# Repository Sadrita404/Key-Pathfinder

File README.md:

| Title | Key Pathfinder |
| :-- | :---|
|Author |Sadrita Neogi|

### About
A small basic strategy machine using only 4 buttons and 4 leds. It uses a Seeed Studios Xiao RP2040 for logic it is also use to control the keyboard shortcuts.

### Why I chose this project?
Behind choosing this project, when I have started stasis I was not sure about what I can. Then. I see the starter project where I find this pathfinder that to be built, so I make it with some extra features like in the starter project, it has only three keys, so I added one extra keys just to use the more functionality of the device, so I have build this project.

### How to use this project
This project can be used in multiple waste based upon the user need best for me. I will use it for the shortcut that I have implemented and also it also works as a stress reliever. When I am bored, I can place the key and the LED will blink, according to the input that I am giving.

<div align="center">

| | PCB Designing | |
| :---: | :---: | :---: |
|  |  |  |
|  |  |  |
|  |  |  |

<!-- TWO-COLUMN IMAGE FRAME GRID -->
<div align="center">
  <table border="0" cellpadding="10" cellspacing="0" style="border-collapse: collapse;">
    <tr>
      <!-- FRONT SIDE CARD -->
      <td align="center" valign="top" width="50%" style="background: #ffffff; border: 1px solid #d0d7de; border-radius: 12px; padding: 16px; box-shadow: 0 4px 12px rgba(0,0,0,0.05);">
        
        <div style="margin-top: 12px; font-family: -apple-system, BlinkMacSystemFont, 'Segoe UI', Helvetica, Arial, sans-serif; font-size: 13px; color: #57606a; font-weight: 600; text-transform: uppercase; letter-spacing: 0.5px;">
          ▲ Front Side View
        </div>
      </td>
      <!-- SPACER FOR GITHUB MOBILE DEGRADATION -->
      <td width="2%">&nbsp;</td>
      <!-- BACK SIDE CARD -->
      <td align="center" valign="top" width="50%" style="background: #ffffff; border: 1px solid #d0d7de; border-radius: 12px; padding: 16px; box-shadow: 0 4px 12px rgba(0,0,0,0.05);">
        
        <div style="margin-top: 12px; font-family: -apple-system, BlinkMacSystemFont, 'Segoe UI', Helvetica, Arial, sans-serif; font-size: 13px; color: #57606a; font-weight: 600; text-transform: uppercase; letter-spacing: 0.5px;">
          ▲ Back Side View
        </div>
      </td>
    </tr>
  </table>
</div>
</div>

<div align="center">
  <h2> Bill of Materials </h2>
</div>

| Component Name | Purpose | Qty | Unit Price | Total Price in USD | Link |
| :--- | :--- | :---: | :---: | :---: | :---: |
| **Resistors(220 Ohm 0.25W )** | To control the current flow | 4 | $0.0096 | $0.04 | [Link](https://robu.in/product/220-ohm-resistor-0-25w-metal-film-pack-of-100/?gad_source=1&gad_campaignid=17427802703&gbraid=0AAAAADvLFWekTwWN9jC03A8IQT8r3AlY5&gclid=CjwKCAjw6f3RBhApEiwAMaCqWcaO2dly3_fFTVA-yL3R27B3th02OcCqODYx5UqYKDzOy5vnEFLU-hoCv24QAvD_BwE) |
| **3mm Green DIP LED** | For the light | 4 | $0.016 | $0.06 | [Link](https://robu.in/product/5mm-green-surface-mount-led-pack-of-50/?gad_source=1&gad_campaignid=17427802703&gbraid=0AAAAADvLFWekTwWN9jC03A8IQT8r3AlY5&gclid=CjwKCAjw6f3RBhApEiwAMaCqWRUCdY8CmAQTw0-cabIrtaeX7ebfmDpTQ9LgE_gcqU91_RtSVQTk3hoCW7cQAvD_BwE)|
| **Blank Keycaps (10)** | To put it in the switches | 1 | $1.59 | $1.59 | [Link](https://stackskb.com/store/numpad-keycaps/) |
| **Seeed Studio XIAO RP2040** | To control the board | 1 | $6.55 | $6.55 | [Link](https://robu.in/product/seeed-studio-xiao-rp2040-v1-0/) |
| **PCB Board** | The main board | 1 | $2.00 | $2.00 | [Link](https://jlcpcb.com/) |
| **Linear Switch (moq 10)** | To press the switch | 1 | $3.18 | $3.18 | [Link](https://stackskb.com/store/hmx-switch-tester/) |

<div align="center">
  <table border="0" cellpadding="0" cellspacing="0" style="border-collapse: collapse; max-width: 600px;">
    <tr>
      <td style="background: #ffffff; border: 1px solid #d0d7de; border-radius: 12px; padding: 20px; box-shadow: 0 4px 12px rgba(0,0,0,0.05); font-family: -apple-system, BlinkMacSystemFont, 'Segoe UI', Helvetica, Arial, sans-serif;">
        <div style="font-size: 16px; font-weight: 600; color: #24292f; margin-bottom: 12px; border-bottom: 1px solid #d0d7de; padding-bottom: 8px;">
           Final Summary Title
        </div>
        <table width="100%" border="0" style="border-collapse: collapse; font-size: 14px; color: #57606a;">
          <tr>
            <td style="padding: 4px 0;">Component Subtotal:</td>
            <td align="right" style="font-weight: 500; color: #24292f;">$13.42</td>
          </tr>
          <tr>
            <td style="padding: 4px 0;">Shipping Cost(incl. PCB):</td>
            <td align="right" style="font-weight: 500; color: #24292f;">$11</td>
          </tr>
          <tr>
            <td style="padding: 4px 0; padding-bottom: 8px;">Tax:</td>
            <td align="right" style="font-weight: 500; color: #24292f;">$0.5</td>
          </tr>
          <tr style="border-top: 1px dashed #d0d7de;">
            <td style="padding: 12px 0 0 0; font-weight: 600; color: #24292f; font-size: 15px;">Net Total Cost:</td>
            <td align="right" style="padding: 12px 0 0 0; font-weight: bold; color: #2da44e; font-size: 18px;">$24.92</td>
          </tr>
          <tr>
            <td style="padding: 2px 0 0 0; font-size: 11px; color: #8c959f;">Projected Budget Allocation:</td>
            <td align="right" style="padding: 2px 0 0 0; font-weight: 500; font-size: 12px; color: #8c959f;">$25</td>
          </tr>
        </table>
      </td>
    </tr>
  </table>
</div>

---

**Project Under Hack Club**

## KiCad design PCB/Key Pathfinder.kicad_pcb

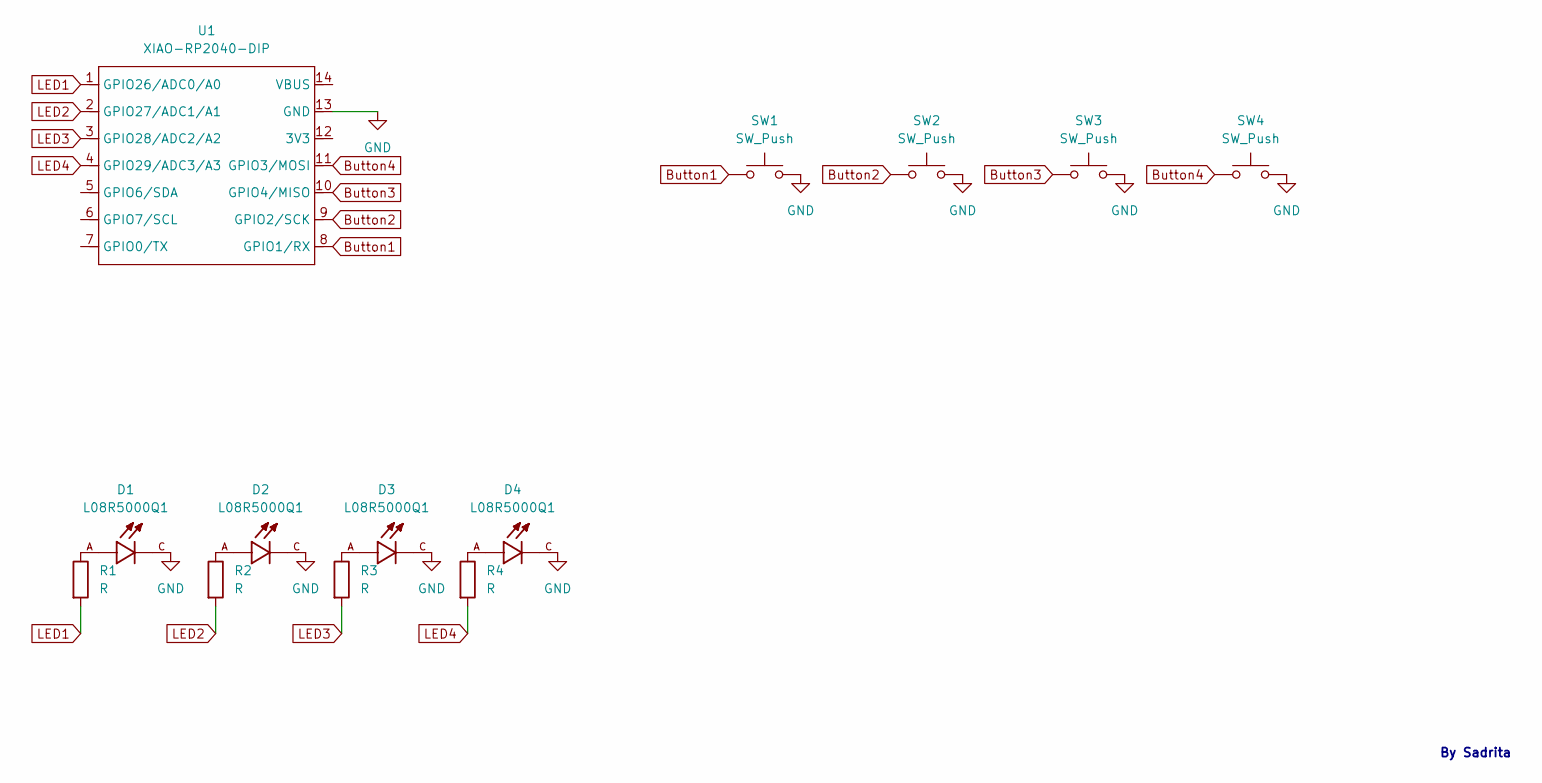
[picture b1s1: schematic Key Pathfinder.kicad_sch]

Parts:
D1, D2, D3, D4: L08R5000Q1; LED; PARTREV NA
R1, R2, R3, R4: R; R_Axial_DIN0204_L3.6mm_D1.6mm_P5.08mm_Vertical
SW1, SW2, SW3, SW4: SW_Push; SW_Cherry_MX_1.00u_PCB3D
U1: XIAO-RP2040-DIP

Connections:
Button1: SW1.1, U1.8 (GPIO1/RX)
Button2: SW2.1, U1.9 (GPIO2/SCK)
Button3: SW3.1, U1.10 (GPIO4/MISO)
Button4: SW4.1, U1.11 (GPIO3/MOSI)
GND: D1.C, D2.C, D3.C, D4.C, SW1.2, SW2.2, SW3.2, SW4.2, U1.13 (GND)
LED1: R1.2, U1.1 (GPIO26/ADC0/A0)
LED2: R2.2, U1.2 (GPIO27/ADC1/A1)
LED3: R3.2, U1.3 (GPIO28/ADC2/A2)
LED4: R4.2, U1.4 (GPIO29/ADC3/A3)
unnamed: D1.A, R1.1
unnamed: D2.A, R2.1
unnamed: D3.A, R3.1
unnamed: D4.A, R4.1

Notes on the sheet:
By Sadrita

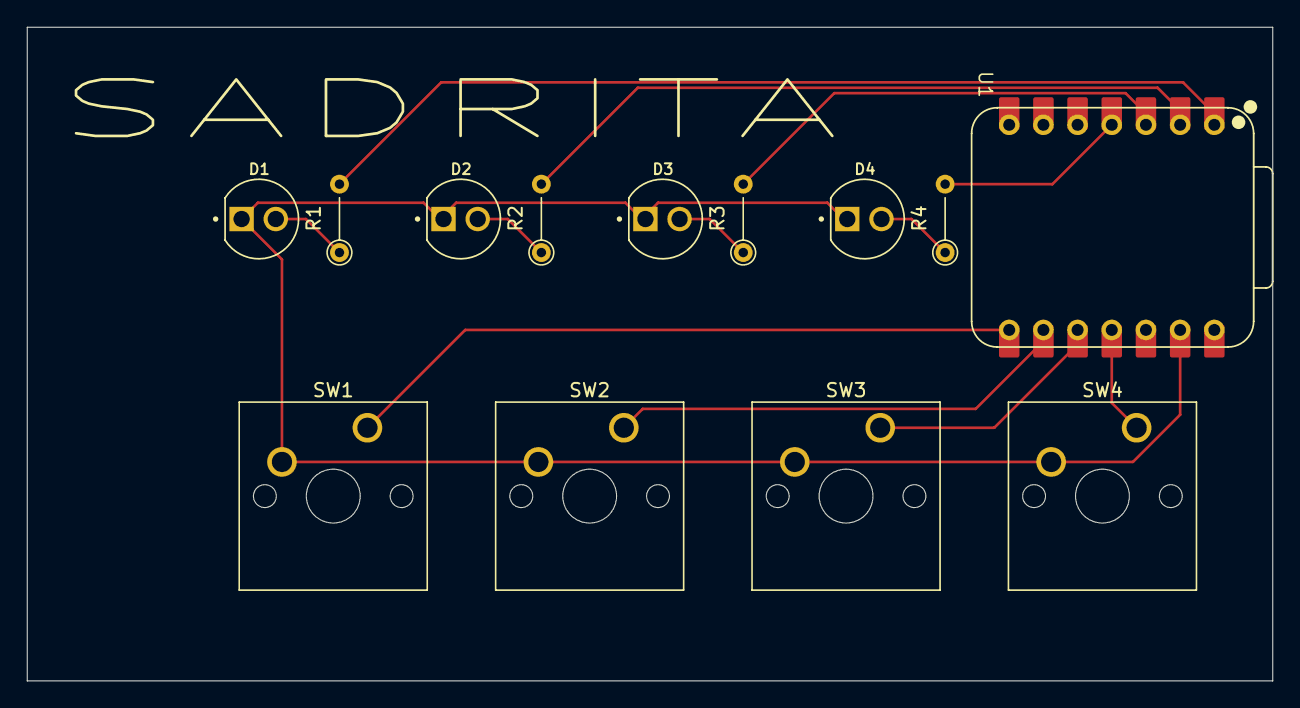
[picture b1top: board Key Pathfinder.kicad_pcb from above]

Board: 2 copper layers, 92.5 x 48.6 mm, 13 parts (0 on the bottom side), 13 nets.

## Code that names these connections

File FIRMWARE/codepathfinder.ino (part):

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const int BUT3 = D9;
const int BUT4 = D10;

const int LED1 = D0;
const int LED2 = D1;
const int LED3 = D2;
const int LED4 = D3;

const int BRIGHTNESS = 30;

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  pinMode(BUT2, INPUT_PULLUP);
  pinMode(BUT3, INPUT_PULLUP);
  pinMode(BUT4, INPUT_PULLUP);
  pinMode(LED1, OUTPUT);
  pinMode(LED2, OUTPUT);
  pinMode(LED3, OUTPUT);
  pinMode(LED4, OUTPUT);
  showRules();
}

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
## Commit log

2026-06-25 Firmware added
2026-06-27 updated bill added
2026-06-27 new bom added
